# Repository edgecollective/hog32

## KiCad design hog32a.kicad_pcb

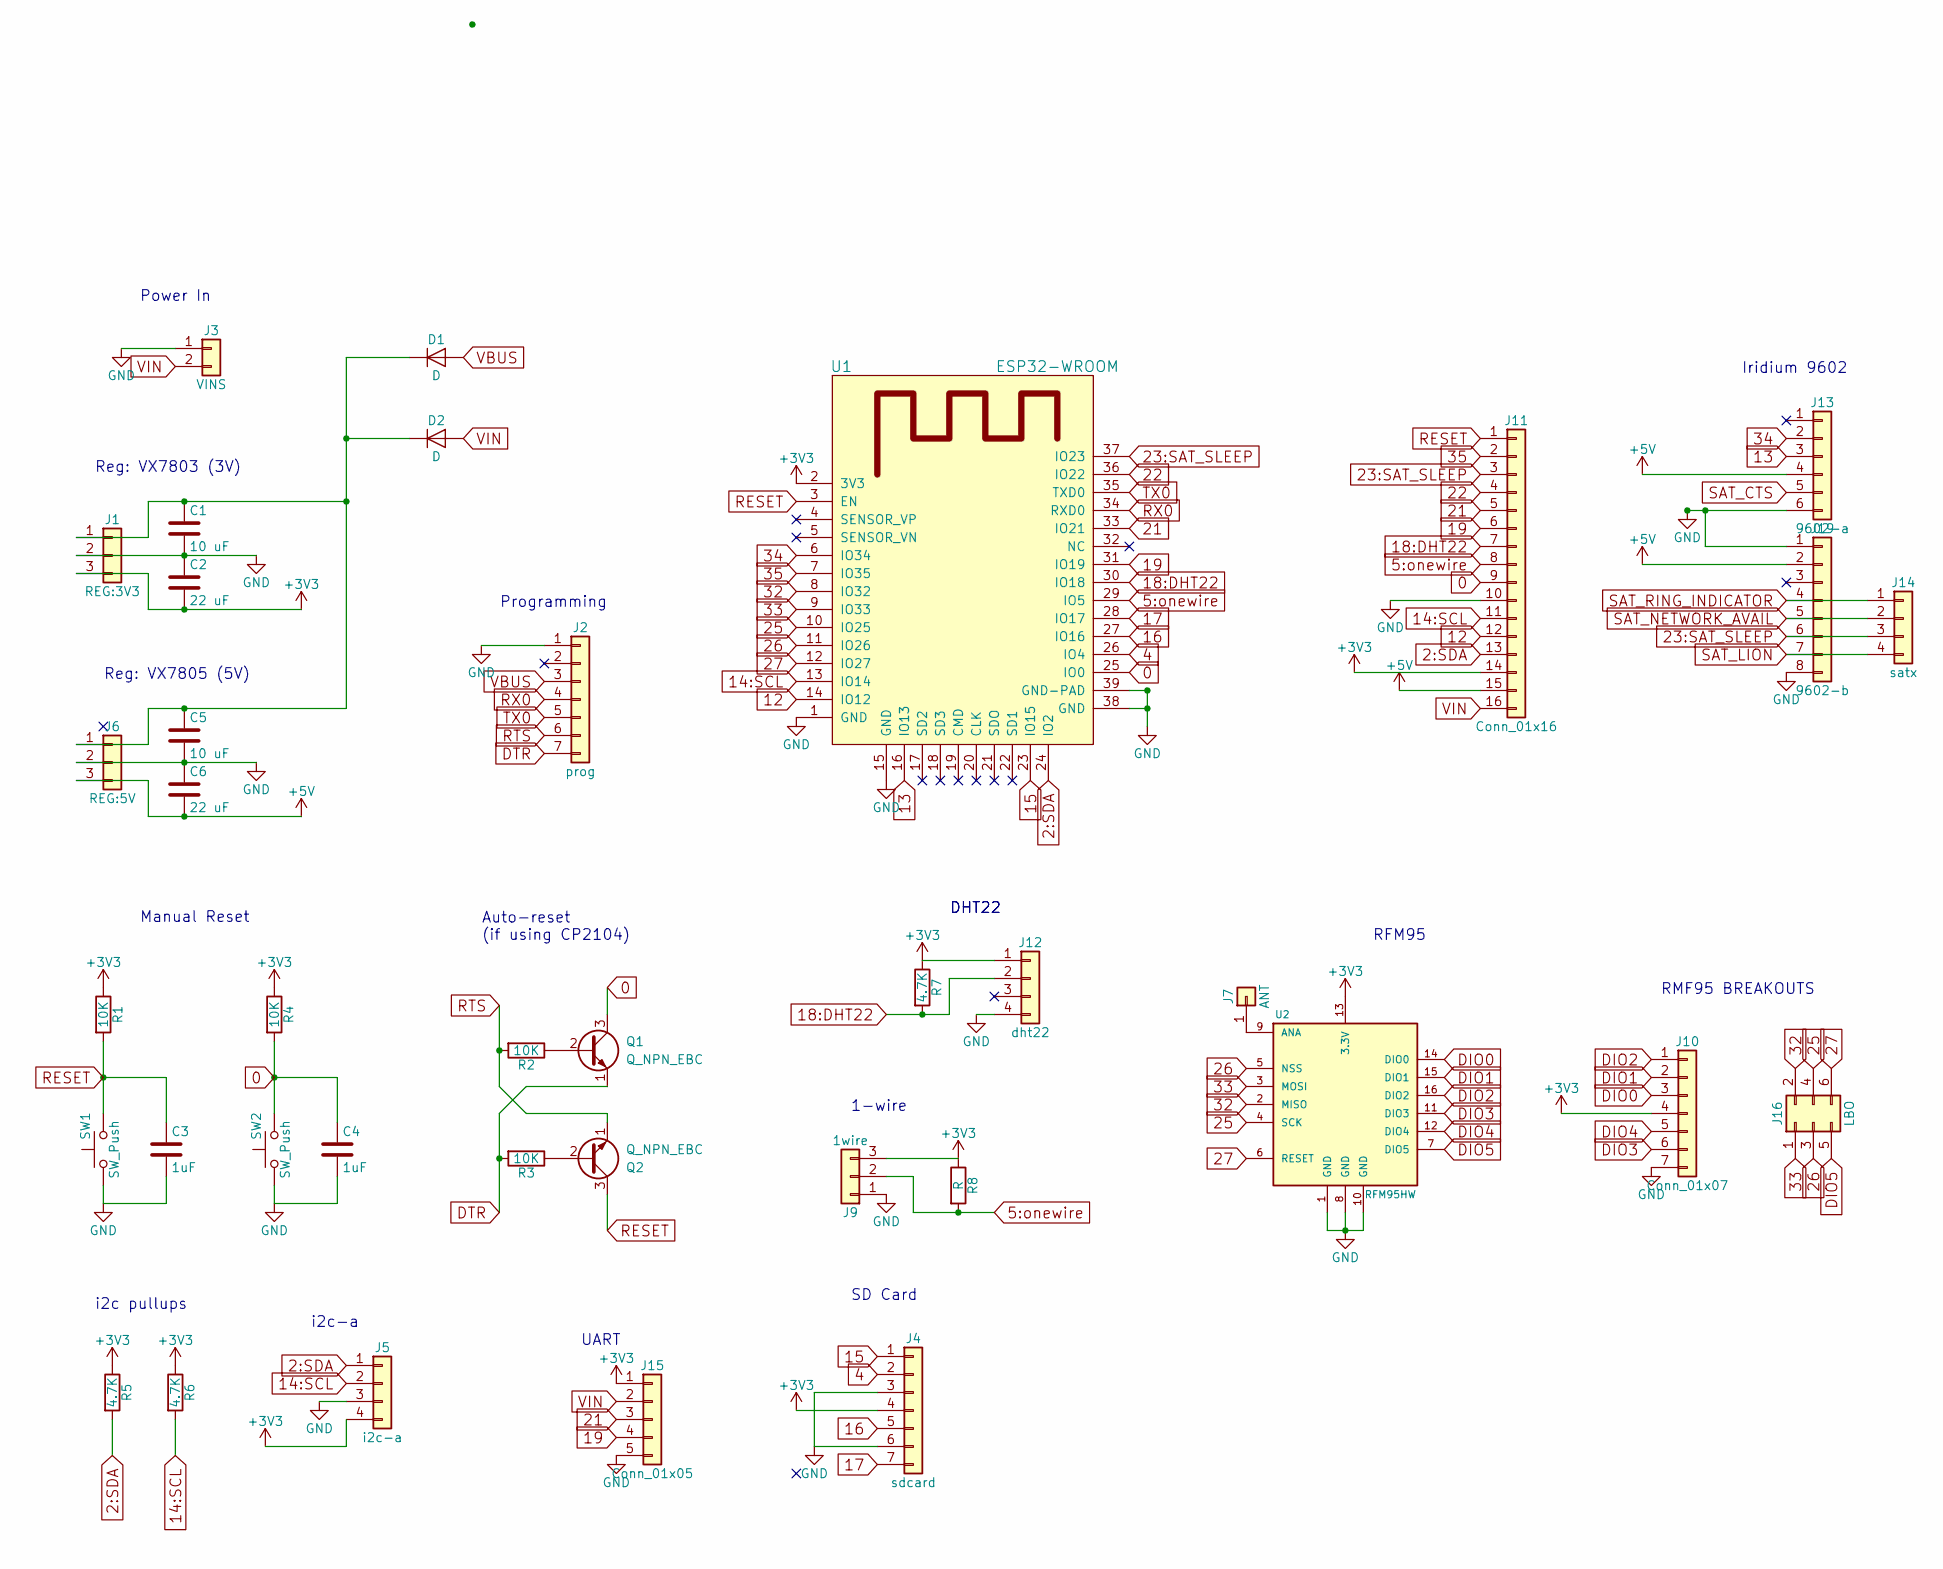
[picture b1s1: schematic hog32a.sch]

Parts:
C1, C5: 10 uF; C_Disc_D3.0mm_W1.6mm_P2.50mm
C2, C6: 22 uF; C_Disc_D3.0mm_W1.6mm_P2.50mm
C3, C4: 1uF; C_Disc_D3.0mm_W1.6mm_P2.50mm
D1, D2: D; D_DO-201_P5.08mm_Vertical_AnodeUp
J1: REG:3V3; Socket_Strip_Straight_1x03_Pitch2.54mm
J2: prog; Pin_Header_Straight_1x07_Pitch2.54mm
J3: VINS; TerminalBlock_Phoenix_PT-3.5mm_2pol
J4: sdcard; Pin_Header_Straight_1x07_Pitch2.54mm
J5: i2c-a; Pin_Header_Straight_1x04_Pitch2.54mm
J6: REG:5V; Pin_Header_Straight_1x03_Pitch2.54mm
J7: ANT; Pin_Header_Straight_1x01_Pitch2.54mm
J9: 1wire; TerminalBlock_Phoenix_PT-3.5mm_3pol
J10: Conn_01x07; Pin_Header_Straight_1x07_Pitch2.54mm
J11: Conn_01x16; Pin_Header_Straight_1x16_Pitch2.54mm
J12: dht22; Pin_Header_Straight_1x04_Pitch2.54mm
J13: 9602-a; Pin_Header_Straight_1x06_Pitch2.54mm
J14: satx; Pin_Header_Straight_1x04_Pitch2.54mm
J15: Conn_01x05; TerminalBlock_Phoenix_PT-3.5mm_5pol
J16: LBO; Pin_Header_Straight_2x03_Pitch2.54mm
J19: 9602-b; Pin_Header_Straight_1x08_Pitch2.54mm
Q1, Q2: Q_NPN_EBC
R1, R2, R3, R4: 10K; R_Axial_DIN0204_L3.6mm_D1.6mm_P1.90mm_Vertical
R5, R6, R7: 4.7K; R_Axial_DIN0204_L3.6mm_D1.6mm_P1.90mm_Vertical
R8: R; R_Axial_DIN0204_L3.6mm_D1.6mm_P1.90mm_Vertical
SW1, SW2: SW_Push; SW_PUSH_6mm
U1: ESP32-WROOM
U2: RFM95HW; RFM95

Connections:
0: C4.1, J11.9, Q1.3 (C), R4.2, SW2.2, U1.25 (IO0)
2:SDA: J5.1, J11.13, R5.2, U1.24 (IO2)
4: J4.2, U1.26 (IO4)
5:onewire: J9.2, J11.8, R8.2, U1.29 (IO5)
12: J11.12, U1.14 (IO12)
13: J13.3, U1.16 (IO13)
14:SCL: J5.2, J11.11, R6.2, U1.13 (IO14)
15: J4.1, U1.23 (IO15)
16: J4.5, U1.27 (IO16)
17: J4.7, U1.28 (IO17)
18:DHT22: J11.7, J12.2, R7.2, U1.30 (IO18)
19: J11.6, J15.4, U1.31 (IO19)
21: J11.5, J15.3, U1.33 (IO21)
22: J11.4, U1.36 (IO22)
23:SAT_SLEEP: J11.3, J14.3, J19.6, U1.37 (IO23)
25: J16.4, U1.10 (IO25), U2.4 (SCK)
26: J16.3, U1.11 (IO26), U2.5 (NSS)
27: J16.6, U1.12 (IO27), U2.6 (RESET)
32: J16.2, U1.8 (IO32), U2.2 (MISO)
33: J16.1, U1.9 (IO33), U2.3 (MOSI)
34: J13.2, U1.6 (IO34)
35: J11.2, U1.7 (IO35)
+3V3: C2.2, J1.3, J4.4, J5.4, J9.3, J10.4, J11.14, J12.1, J15.1, R1.1, R4.1, R5.1, R6.1, R7.1, R8.1, U1.2 (3V3), U2.13 (3.3V)
+5V: C6.2, J6.3, J11.15, J13.4, J19.2
DIO0: J10.3, U2.14 (DIO0)
DIO1: J10.2, U2.15 (DIO1)
DIO2: J10.1, U2.16 (DIO2)
DIO3: J10.6, U2.11 (DIO3)
DIO4: J10.5, U2.12 (DIO4)
DIO5: J16.5, U2.7 (DIO5)
DTR: J2.7, Q1.1 (E), R3.2
GND: C1.2, C2.1, C3.2, C4.2, C5.2, C6.1, J1.2, J2.1, J3.1, J4.3, J4.6, J5.3, J6.2, J9.1, J10.7, J11.10, J12.4, J13.6, J15.5, J19.1, J19.8, SW1.1, SW2.1, U1.1 (GND), U1.15 (GND), U1.38 (GND), U1.39 (GND-PAD), U2.1 (GND), U2.8 (GND), U2.10 (GND)
unnamed: C1.1, C5.1, D1.1 (K), D2.1 (K), J1.1, J6.1
unnamed: J7.1, U2.9 (ANA)
unnamed: Q1.2 (B), R2.1
unnamed: Q2.2 (B), R3.1
RESET: C3.1, J11.1, Q2.3 (C), R1.2, SW1.2, U1.3 (EN)
RTS: J2.6, Q2.1 (E), R2.2
RX0: J2.4, U1.34 (RXD0)
SAT_LION: J14.4, J19.7
SAT_NETWORK_AVAIL: J14.2, J19.5
SAT_RING_INDICATOR: J14.1, J19.4
TX0: J2.5, U1.35 (TXD0)
VBUS: D1.2 (A), J2.3
VIN: D2.2 (A), J3.2, J11.16, J15.2

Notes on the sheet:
Auto-reset (if using CP2104)
SD Card
i2c-a
i2c pullups
Programming
1-wire
Power In
Reg: VX7805 (5V)
Iridium 9602
DHT22
UART
RFM95
RMF95 BREAKOUTS
Reg: VX7803 (3V)
Manual Reset

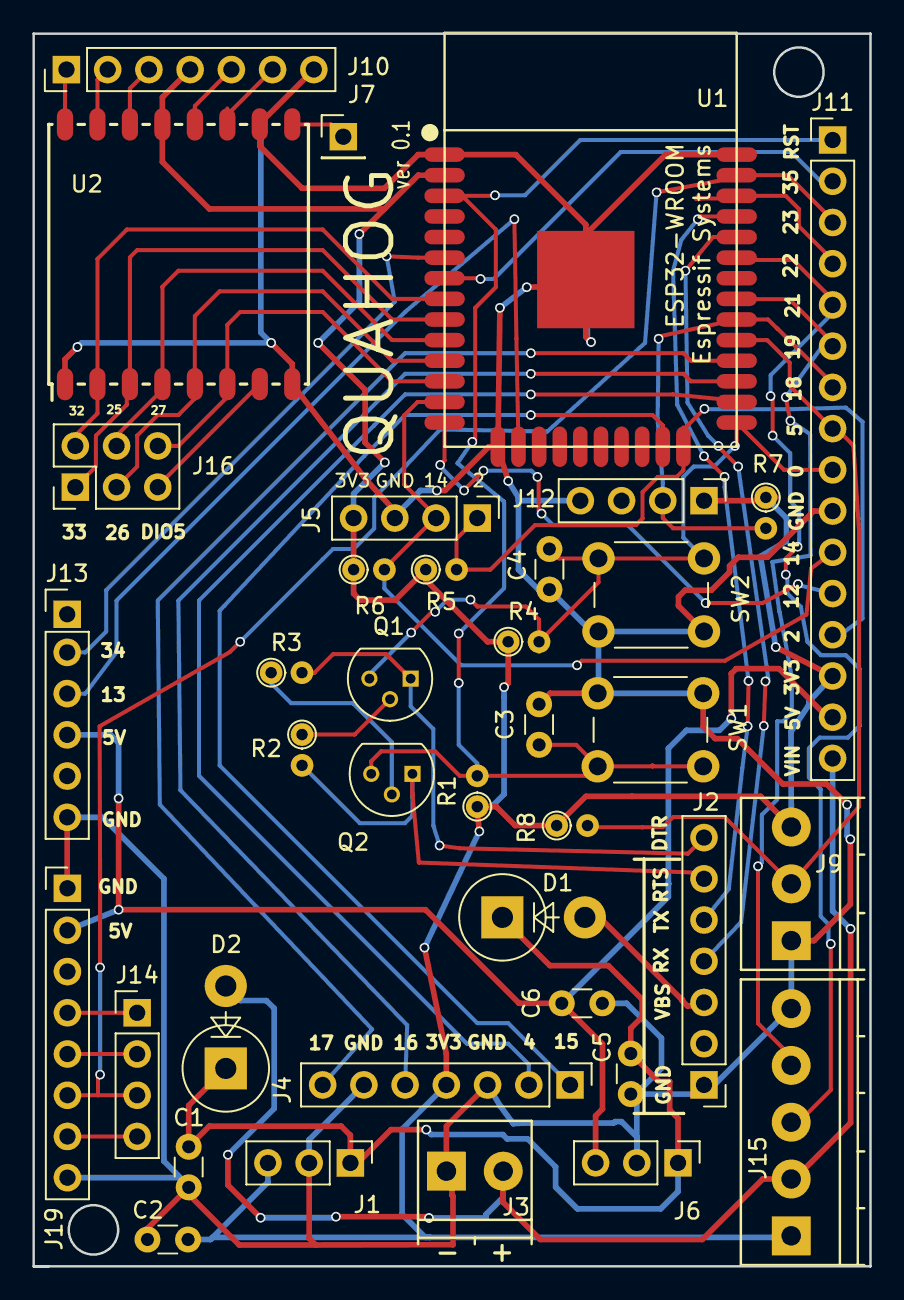
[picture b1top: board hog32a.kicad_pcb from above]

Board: 2 copper layers, 51.6 x 75.9 mm, 38 parts (0 on the bottom side), 45 nets.
